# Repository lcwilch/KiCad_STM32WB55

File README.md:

# KiCad_STM32WB55

Finished https://www.youtube.com/watch?v=nkHFoxe0mrU&amp;t=3668s and successfully manufactured and brought-up board pictured above

# Bluephil
Contains KiCad project and manufacturing files and information

# STM32CubeIDE
Contains a STM32CubeIDE project that tests board SWD interface (for flashing and debug), debug LED GPIO, and USB FS CDC functionality

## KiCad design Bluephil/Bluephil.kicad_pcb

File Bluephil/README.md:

# KiCad
Most files in this dir are related to the KiCad project

# Manufacturing
Contains files needed to manufacture board: Gerbers, BOM, component placement
Also contains assembly drawings and engineering/technical questions and answers when manufacturing via PCBWay

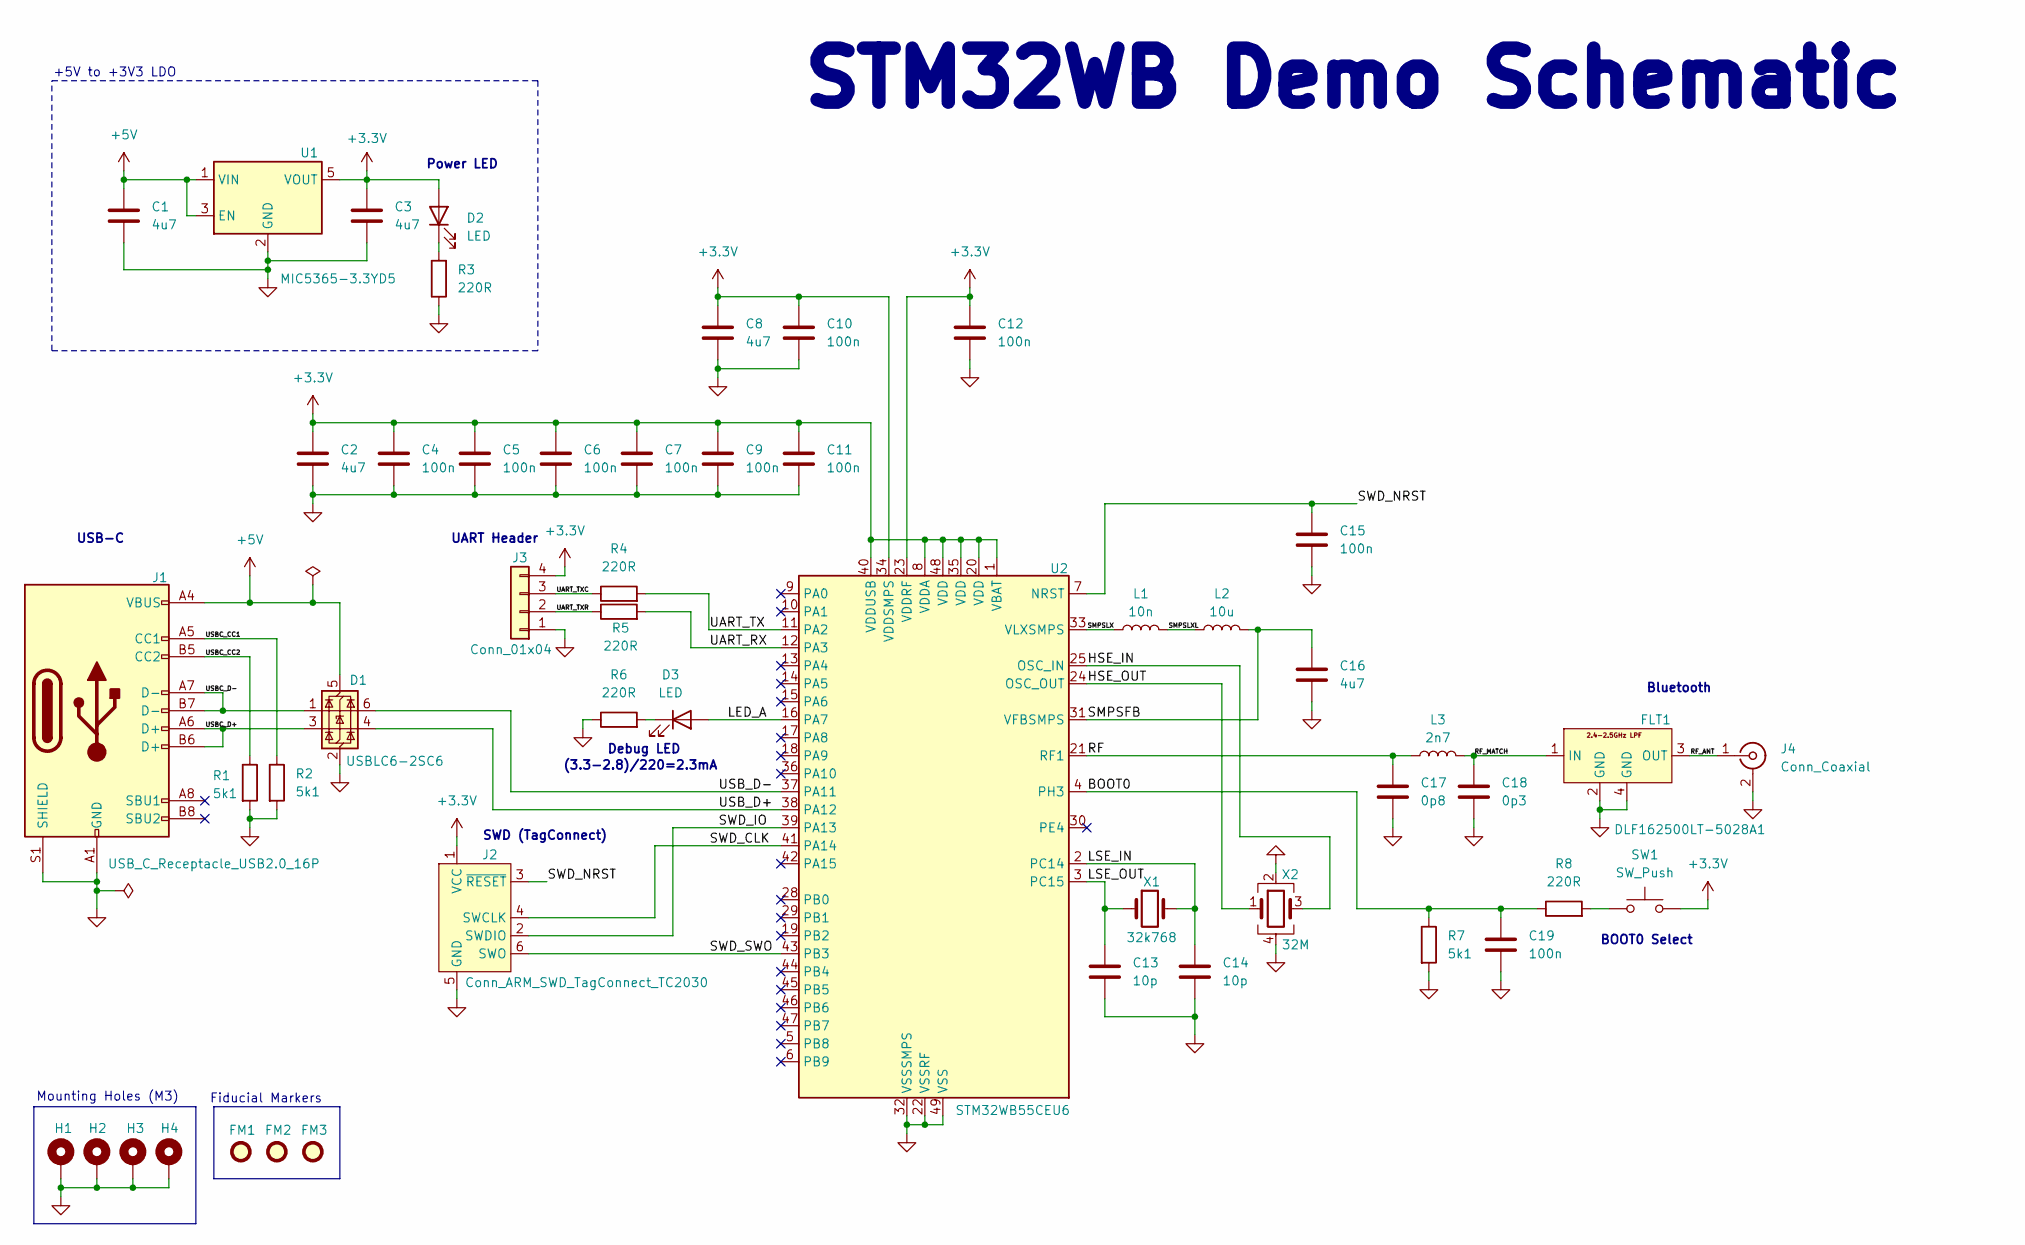
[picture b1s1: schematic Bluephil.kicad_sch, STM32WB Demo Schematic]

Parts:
C1, C2, C3, C8, C16: 4u7; R_0603_1608Metric; Manufacturer PN GRM188Z71A475KE15J
C4, C5, C6, C7, C9, C10, C11, C12, C15, C19: 100n; C_0402_1005Metric; Manufacturer PN GRM155R71A104KA01J
C13, C14: 10p; R_0402_1005Metric; Manufacturer PN 04026D100JAT2A
C17: 0p8; R_0402_1005Metric; Manufacturer PN GRM1555C1HR80BA01D
C18: 0p3; R_0402_1005Metric; Manufacturer PN GRM1555C1HR30WA01D
D1: USBLC6-2SC6; SOT-23-6; Manufacturer PN USBLC6-2SC6
D2, D3: LED; LED_0402_1005Metric; Manufacturer PN APHHS1005LQBC/D-V
FLT1: DLF162500LT-5028A1; Manufacturer PN DLF162500LT-5028A1
FM1, FM2, FM3: Fiducial; Fiducial_1mm_Mask2mm
H1, H2, H3, H4: MountingHole_Pad; MountingHole_2.2mm_M2_DIN965_Pad
J1: USB_C_Receptacle_USB2.0_16P; USB_C_Receptacle_GCT_USB4105-xx-A_16P_TopMnt_Horizontal; Manufacturer PN USB4105-GF-A
J2: Conn_ARM_SWD_TagConnect_TC2030; Tag-Connect_TC2030-IDC-FP_2x03_P1.27mm_Vertical
J3: Conn_01x04; Molex_PicoBlade_53048-0410_1x04_P1.25mm_Horizontal; Manufacturer PN 53048-0410
J4: Conn_Coaxial; U.FL_Hirose_U.FL-R-SMT-1_Vertical; Manufacturer PN U.FL-R-SMT-1(10)
L1: 10n; L_0402_1005Metric; Manufacturer PN LQG15WZ10NJ02D
L2: 10u; L_0805_2012Metric; Manufacturer PN LQM21FN100M70L
L3: 2n7; L_0402_1005Metric; Manufacturer PN LQG15HS2N7S02D
R1, R2, R7: 5k1; R_0402_1005Metric; Manufacturer PN SG73P1EWTTP512J
R3, R4, R5, R6, R8: 220R; R_0402_1005Metric; Manufacturer PN RK73H1ETTP2200F
SW1: SW_Push; SW_Push_1P1T_NO_CK_KMR2; Manufacturer PN KMR231NGLFS
U1: MIC5365-3.3YD5; SOT-23-5; Manufacturer PN MIC5365-3.3YD5-TR
U2: STM32WB55CEU6; QFN-48-1EP_7x7mm_P0.5mm_EP5.6x5.6mm; Manufacturer PN STM32WB55CEU6
X1: 32k768; Crystal_SMD_2012-2Pin_2.0x1.2mm; Manufacturer PN NX2012SA-32.768K-STD-MUB-1
X2: 32M; Crystal_SMD_2016-4Pin_2.0x1.6mm; Manufacturer PN NX2016SA-32M-EXS00A-CS06465

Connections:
+3.3V: C2.1, C3.1, C4.1, C5.1, C6.1, C7.1, C8.1, C9.1, C10.1, C11.1, C12.1, D2.2 (A), J2.1 (VCC), J3.4, SW1.2, U1.5 (VOUT), U2.1 (VBAT), U2.8 (VDDA), U2.20 (VDD), U2.23 (VDDRF), U2.34 (VDDSMPS), U2.35 (VDD), U2.40 (VDDUSB), U2.48 (VDD)
+5V: C1.1, D1.5 (VBUS), J1.A4 (VBUS), J1.A9 (VBUS), J1.B4 (VBUS), J1.B9 (VBUS), U1.1 (VIN), U1.3 (EN)
/BOOT0: C19.1, R7.1, R8.1, U2.4 (PH3)
/HSE_IN: U2.25 (OSC_IN), X2.3
/HSE_OUT: U2.24 (OSC_OUT), X2.1
/LED_A: D3.2 (A), U2.16 (PA7)
/LSE_IN: C14.1, U2.2 (PC14), X1.2
/LSE_OUT: C13.1, U2.3 (PC15), X1.1
/RF: C17.1, L3.1, U2.21 (RF1)
/RF_ANT: FLT1.3 (OUT), J4.1 (In)
/RF_MATCH: C18.1, FLT1.1 (IN), L3.2
/SMPSFB: C16.1, L2.2, U2.31 (VFBSMPS)
/SMPSLX: L1.1, U2.33 (VLXSMPS)
/SMPSLXL: L1.2, L2.1
/SWD_CLK: J2.4 (SWCLK), U2.41 (PA14)
/SWD_IO: J2.2 (SWDIO), U2.39 (PA13)
/SWD_NRST: C15.1, J2.3 (~RESET), U2.7 (NRST)
/SWD_SWO: J2.6 (SWO), U2.43 (PB3)
/UART_RX: R5.2, U2.12 (PA3)
/UART_TX: R4.2, U2.11 (PA2)
/UART_TXC: J3.3, R4.1
/UART_TXR: J3.2, R5.1
/USBC_CC1: J1.A5 (CC1), R2.1
/USBC_CC2: J1.B5 (CC2), R1.1
/USBC_D+: D1.3 (I/O2), J1.A6 (D+), J1.B6 (D+)
/USBC_D-: D1.1 (I/O1), J1.A7 (D-), J1.B7 (D-)
/USB_D+: D1.4 (I/O2), U2.38 (PA12)
/USB_D-: D1.6 (I/O1), U2.37 (PA11)
GND: C1.2, C2.2, C3.2, C4.2, C5.2, C6.2, C7.2, C8.2, C9.2, C10.2, C11.2, C12.2, C13.2, C14.2, C15.2, C16.2, C17.2, C18.2, C19.2, D1.2 (GND), FLT1.2 (GND), FLT1.4 (GND), H1.1, H2.1, H3.1, H4.1, J1.A1 (GND), J1.A12 (GND), J1.B1 (GND), J1.B12 (GND), J1.S1 (SHIELD), J2.5 (GND), J3.1, J4.2 (Ext), R1.2, R2.2, R3.1, R6.1, R7.2, U1.2 (GND), U2.22 (VSSRF), U2.32 (VSSSMPS), U2.49 (VSS), X2.2, X2.4
unnamed: D2.1 (K), R3.2
unnamed: D3.1 (K), R6.2
unnamed: R8.2, SW1.1

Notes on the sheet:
BOOT0 Select
UART Header
Bluetooth
+5V to +3V3 LDO
Power LED
Fiducial Markers
SWD (TagConnect)
Mounting Holes (M3)
STM32WB Demo Schematic
USB-C
Debug LED
(3.3-2.8)/220=2.3mA

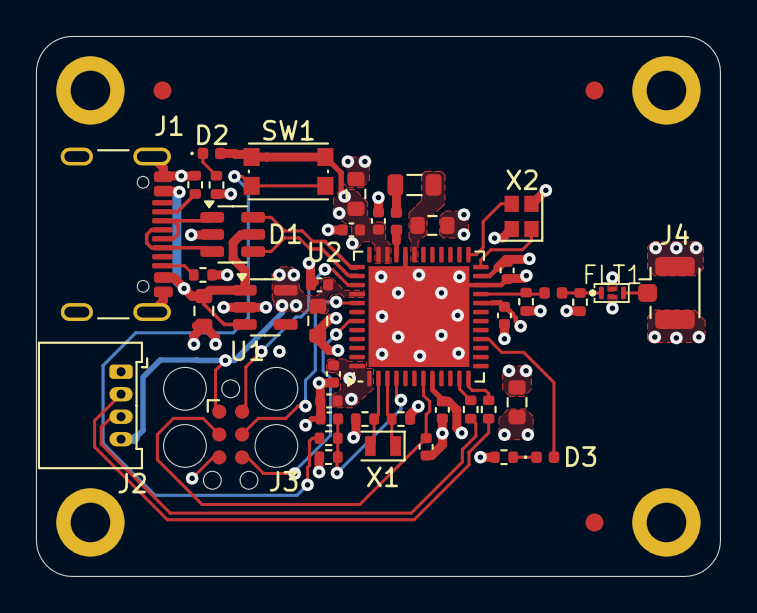
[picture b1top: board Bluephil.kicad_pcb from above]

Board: 4 copper layers, 38.0 x 30.0 mm, 50 parts (0 on the bottom side), 32 nets.

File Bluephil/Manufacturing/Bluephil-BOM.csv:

"Reference","Value","Footprint","Qty","DNP","Description","Manufacturer","Manufacturer PN","Distributor Link"
"C1,C2,C3,C8,C16","4u7","Resistor_SMD:R_0603_1608Metric","5","","Unpolarized capacitor","Murata Electronics","GRM188Z71A475KE15J","https://www.mouser.com/ProductDetail/Murata-Electronics/GRM1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"
"C4,C5,C6,C7,C9,C10,C11,C12,C15,C19","100n","Capacitor_SMD:C_0402_1005Metric","10","","Unpolarized capacitor","Murata Electronics","GRM155R71A104KA01J","https://www.mouser.com/ProductDetail/Murata-Electronics/GRM1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"
"C13,C14","10p","Resistor_SMD:R_0402_1005Metric","2","","Unpolarized capacitor"," KYOCERA AVX","04026D100JAT2A","https://www.mouser.com/ProductDetail/KYOCERA-AVX/04026D100JA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"
"C17","0p8","Resistor_SMD:R_0402_1005Metric","1","","Unpolarized capacitor","Murata Electronics ","GRM1555C1HR80BA01D","https://www.mouser.com/ProductDetail/Murata-Electronics/GRM1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"
"C18","0p3","Resistor_SMD:R_0402_1005Metric","1","","Unpolarized capacitor","Murata Electronics","GRM1555C1HR30WA01D","https://www.mouser.com/ProductDetail/Murata-Electronics/GRM1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"
"D1","USBLC6-2SC6","Package_TO_SOT_SMD:SOT-23-6","1","","Very low capacitance ESD protection diode, 2 data-line, SOT-23-6","STMicroelectronics"," USBLC6-2SC6","https://www.mouser.com/ProductDetail/STMicroelectronics/USBL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"
"D2,D3","LED","LED_SMD:LED_0402_1005Metric","2","","Light emitting diode","Kingbright","APHHS1005LQBC/D-V","https://www.mouser.com/ProductDetail/Kingbright/APHHS1005LQB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"
"FLT1","DLF162500LT-5028A1","Bluephil_PCBFootprints:DLF162500LT-5028A1","1","","Signal Conditioning LTCC LOW PASS FLTR 2400-2500MHz ","TDK","DLF162500LT-5028A1","https://www.mouser.com/ProductDetail/TDK/DLF162500LT-5028A1?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"
"J1","USB_C_Receptacle_USB2.0_16P","Connector_USB:USB_C_Receptacle_GCT_USB4105-xx-A_16P_TopMnt_Horizontal","1","","USB 2.0-only 16P Type-C Receptacle connector","GCT","USB4105-GF-A ","https://www.mouser.com/ProductDetail/GCT/USB4105-GF-A?qs=KUo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"
"J3","Conn_01x04","Connector_Molex:Molex_PicoBlade_53048-0410_1x04_P1.25mm_Horizontal","1","","Generic connector, single row, 01x04, script generated (kicad-library-utils/schlib/autogen/connector/)","Molex","53048-0410","https://www.mouser.com/ProductDetail/Molex/53048-0410?qs=359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"
"J4","Conn_Coaxial","Connector_Coaxial:U.FL_Hirose_U.FL-R-SMT-1_Vertical","1","","coaxial connector (BNC, SMA, SMB, SMC, Cinch/RCA, LEMO, ...)","Hirose Connector","U.FL-R-SMT-1(10) ","https://www.mouser.com/ProductDetail/Hirose-Connector/U.FL-R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"
"L1","10n","Inductor_SMD:L_0402_1005Metric","1","","Inductor","Murata Electronics","LQG15WZ10NJ02D","https://www.mouser.com/ProductDetail/Murata-Electronics/LQG1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"
"L2","10u","Inductor_SMD:L_0805_2012Metric","1","","Inductor","Murata Electronics","LQM21FN100M70L","https://www.mouser.com/ProductDetail/Murata-Electronics/LQM2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"
"L3","2n7","Inductor_SMD:L_0402_1005Metric","1","","Inductor","Murata Electronics","LQG15HS2N7S02D","https://www.mouser.com/ProductDetail/Murata-Electronics/LQG1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"
"R1,R2,R7","5k1","Resistor_SMD:R_0402_1005Metric","3","","Resistor","KOA Speer","SG73P1EWTTP512J","https://www.mouser.com/ProductDetail/KOA-Speer/SG73P1EWTTP51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"
"R3,R4,R5,R6,R8","220R","Resistor_SMD:R_0402_1005Metric","5","","Resistor","KOA Speer","RK73H1ETTP2200F","https://www.mouser.com/ProductDetail/KOA-Speer/RK73H1ETTP220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"
"SW1","SW_Push","Button_Switch_SMD:SW_Push_1P1T_NO_CK_KMR2","1","","Push button switch, generic, two pins","C&K","KMR231NGLFS ","https://www.mouser.com/ProductDetail/CK/KMR231NGLFS?qs=sb%25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"
"U1","MIC5365-3.3YD5","Package_TO_SOT_SMD:SOT-23-5","1","","150mA Low-dropout Voltage Regulator, Vout 3.3V, Vin up to 5.5V, SOT-23-5","Microchip Technology","MIC5365-3.3YD5-TR","https://www.mouser.com/ProductDetail/Microchip-Technology/MI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"
"U2","STM32WB55CEU6","Package_DFN_QFN:QFN-48-1EP_7x7mm_P0.5mm_EP5.6x5.6mm","1","","STMicroelectronics Arm Cortex-M4 MCU, 512KB flash, 256KB RAM, 64 MHz, 1.71-3.6V, 30 GPIO, UFQFPN48","STMicroelectronics","STM32WB55CEU6","https://www.mouser.com/ProductDetail/STMicroelectronics/STM3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"
"X1","32k768","Crystal:Crystal_SMD_2012-2Pin_2.0x1.2mm","1","","Two pin crystal","NDK","NX2012SA-32.768K-STD-MUB-1 ","https://www.mouser.com/ProductDetail/NDK/NX2012SA-32.768K-ST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"
"X2","32M","Crystal:Crystal_SMD_2016-4Pin_2.0x1.6mm","1","","Four pin crystal, GND on pins 2 and 4","NDK","NX2016SA-32M-EXS00A-CS06465","https://www.mouser.com/ProductDetail/NDK/NX2016SA-32M-EXS00A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"

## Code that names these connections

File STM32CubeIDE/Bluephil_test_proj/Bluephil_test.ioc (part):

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Mcu.Name=STM32WB55CEUx
Mcu.Package=UFQFPN48
Mcu.UserName=STM32WB55CEUx
PA11.Mode=Device
PA11.Signal=USB_DM
PA12.Mode=Device
PA12.Signal=USB_DP
PA7.GPIOParameters=GPIO_Label
PA7.GPIO_Label=Debug_LED
PA7.Signal=GPIO_Output
PC14-OSC32_IN.Mode=LSE-External-Oscillator
PC14-OSC32_IN.Signal=RCC_OSC32_IN
PC15-OSC32_OUT.Mode=LSE-External-Oscillator
PC15-OSC32_OUT.Signal=RCC_OSC32_OUT
RCC.HSE_VALUE=32000000
RCC.SYSCLKFreq_VALUE=64000000
RCC.SYSCLKSource=RCC_SYSCLKSOURCE_PLLCLK
board=custom

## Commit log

2024-04-26 Just submitted board for quote from PCBWay.
2024-05-20 Added STM32CubeIDE project that tests board debug LED and USB FS CDC functionality.
2024-05-20 Organizing repo to finsih project.
2024-06-22 Added .DS_Store to gitignore
2024-06-22 Remved .DS_Store files
